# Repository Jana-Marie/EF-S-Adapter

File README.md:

# EF-S-Adapter

Hard- and Firmware to control EF/EF-S lenses. The protocol used has grown since the first generation of EF(-S) lenses hence is a bit extensive with different layers of compatibility. On the physical layer a SPI like interface is used with I2S alike clock-stretching. 

**Please use at your own risk, the hard- and firmware are experimental and can damage your lens!**

### Status

##### v1
 
  - Tested
  - May shorts power rails on lens attachment
  
##### v1.1

 - Tested

### Todo

 - [x] Make lens hotplugable (needs new hardware revision)
 - [ ] Create helper functions (like set_aperture_to(aperture))
 - [ ] Documentation

### Thanks

Thanks to [Jean](https://pickandplace.wordpress.com/2011/10/05/canon-ef-s-protocol-and-electronic-follow-focus/) for this blogpost!

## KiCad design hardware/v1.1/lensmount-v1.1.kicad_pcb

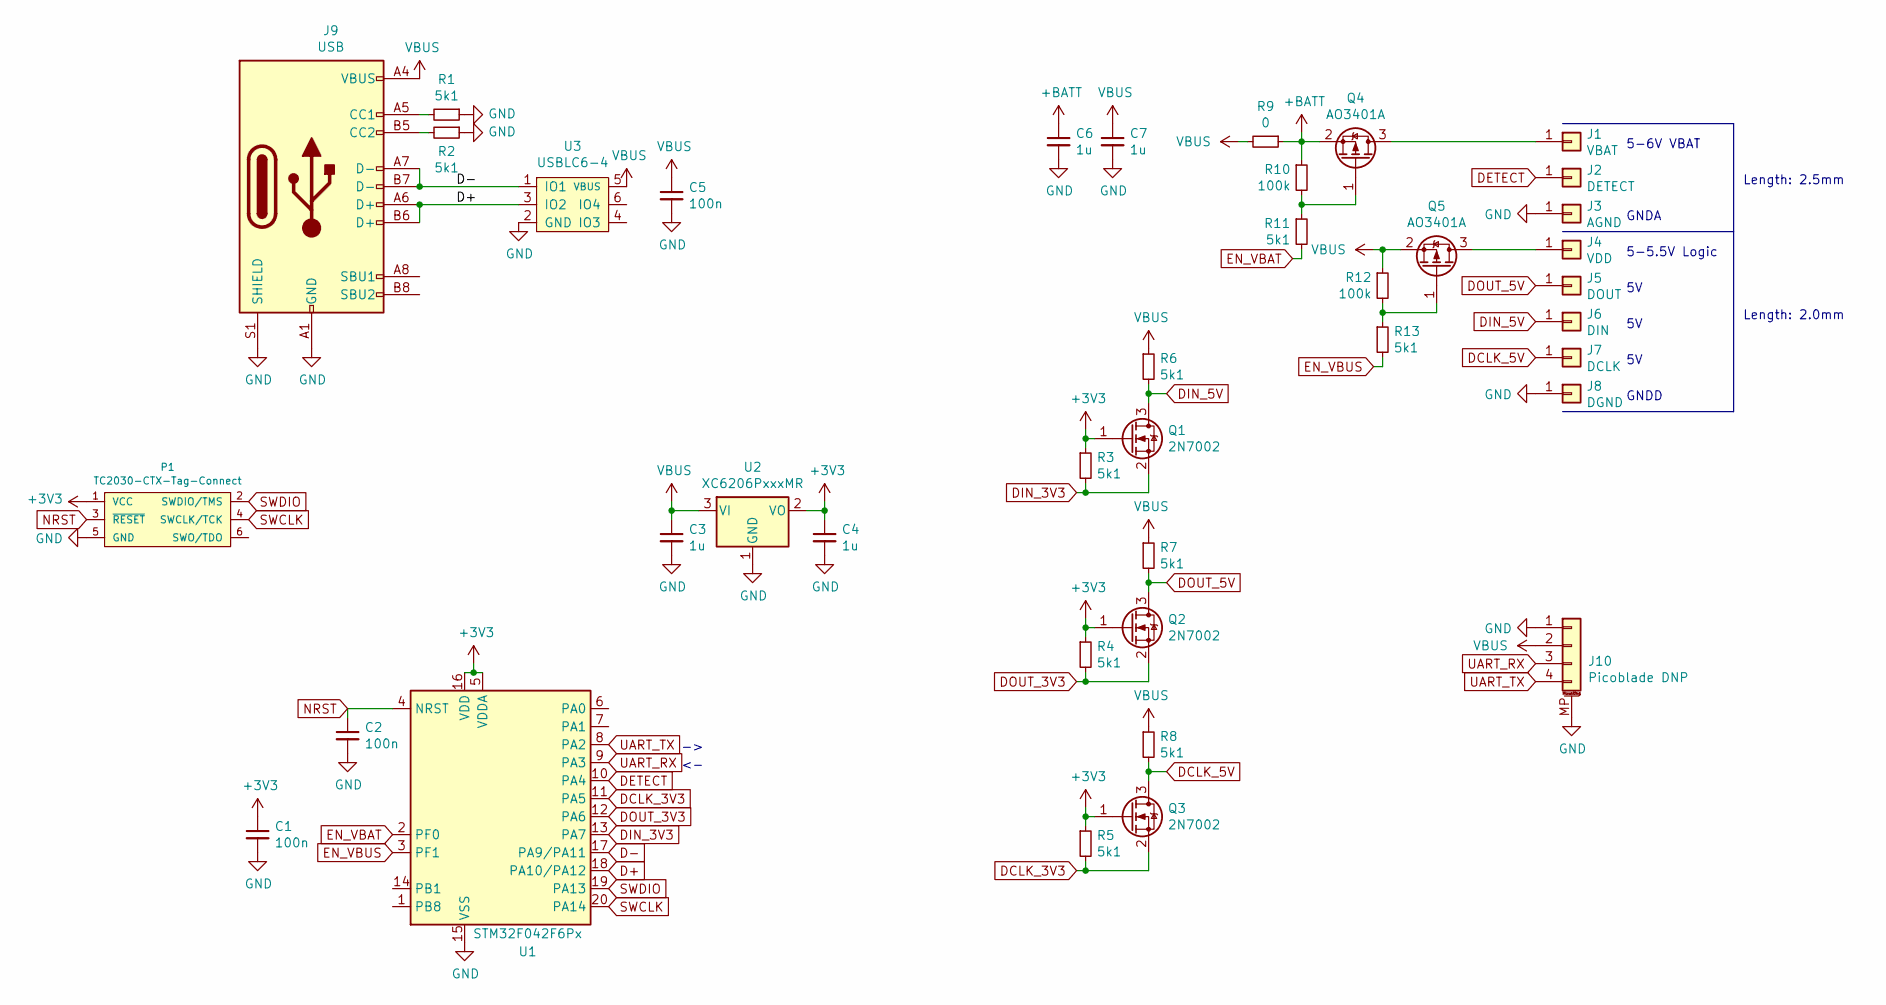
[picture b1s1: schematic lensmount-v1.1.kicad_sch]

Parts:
C1, C2, C5: 100n; C_0402
C3, C4, C6, C7: 1u; C_0603
J1: VBAT; PH-MVF-5365; Mouser 581-709150001025006
J2: DETECT; PH-MVF-5365; Mouser 581-709150001025006
J3: AGND; PH-MVF-5365; Mouser 581-709150001025006
J4: VDD; PH-MVF-5365; Mouser 581-709150001020006
J5: DOUT; PH-MVF-5365; Mouser 581-709150001020006
J6: DIN; PH-MVF-5365; Mouser 581-709150001020006
J7: DCLK; PH-MVF-5365; Mouser 581-709150001020006
J8: DGND; PH-MVF-5365; Mouser 581-709150001020006
J9: USB; USB-C 16Pin
J10: Picoblade DNP; Molex_PicoBlade_53398-0471_1x04-1MP_P1.25mm_Vertical
P1: TC2030-CTX-Tag-Connect; TC2030
Q1, Q2, Q3: 2N7002; SOT-23
Q4, Q5: AO3401A; SOT-23
R1, R2, R3, R4, R5, R6, R7, R8, R11, R13: 5k1; R_0402
R9: 0; R_0402
R10, R12: 100k; R_0402
U1: STM32F042F6Px; TSSOP-20_4.4x6.5mm_P0.65mm
U2: XC6206PxxxMR; SOT-23
U3: USBLC6-4; SOT-23-6

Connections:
+3V3: C1.1, C4.1, P1.1 (VCC), Q1.1 (G), Q2.1 (G), Q3.1 (G), R3.1, R4.1, R5.1, U1.5 (VDDA), U1.16 (VDD), U2.2 (VO)
+BATT: C6.1, Q4.2 (S), R9.1, R10.1
D+: J9.A6 (D+), J9.B6 (D+), U1.18 (PA10/PA12), U3.3 (IO2)
D-: J9.A7 (D-), J9.B7 (D-), U1.17 (PA9/PA11), U3.1 (IO1)
DCLK_3V3: Q3.2 (S), R5.2, U1.11 (PA5)
DCLK_5V: J7.1, Q3.3 (D), R8.2
DETECT: J2.1, U1.10 (PA4)
DIN_3V3: Q1.2 (S), R3.2, U1.13 (PA7)
DIN_5V: J6.1, Q1.3 (D), R6.2
DOUT_3V3: Q2.2 (S), R4.2, U1.12 (PA6)
DOUT_5V: J5.1, Q2.3 (D), R7.2
EN_VBAT: R11.2, U1.2 (PF0)
EN_VBUS: R13.2, U1.3 (PF1)
GND: C1.2, C2.2, C3.2, C4.2, C5.2, C6.2, C7.2, J3.1, J8.1, J9.A1 (GND), J9.A12 (GND), J9.B1 (GND), J9.B12 (GND), J9.S1 (SHIELD), J10.1, J10.MP (MountPin), P1.5 (GND), R1.1, R2.1, U1.15 (VSS), U2.1 (GND), U3.2 (GND)
NRST: C2.1, P1.3 (~RESET), U1.4 (NRST)
unnamed: J1.1, Q4.3 (D)
unnamed: J4.1, Q5.3 (D)
unnamed: J9.A5 (CC1), R1.2
unnamed: J9.B5 (CC2), R2.2
unnamed: Q4.1 (G), R10.2, R11.1
unnamed: Q5.1 (G), R12.2, R13.1
SWCLK: P1.4 (SWCLK/TCK), U1.20 (PA14)
SWDIO: P1.2 (SWDIO/TMS), U1.19 (PA13)
UART_RX: J10.3, U1.9 (PA3)
UART_TX: J10.4, U1.8 (PA2)
VBUS: C3.1, C5.1, C7.1, J9.A4 (VBUS), J9.A9 (VBUS), J9.B4 (VBUS), J9.B9 (VBUS), J10.2, Q5.2 (S), R6.1, R7.1, R8.1, R9.2, R12.1, U2.3 (VI), U3.5 (VBUS)

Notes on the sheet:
5-6V VBAT
Length: 2.5mm
GNDD
Length: 2.0mm
5-5.5V Logic
GNDA

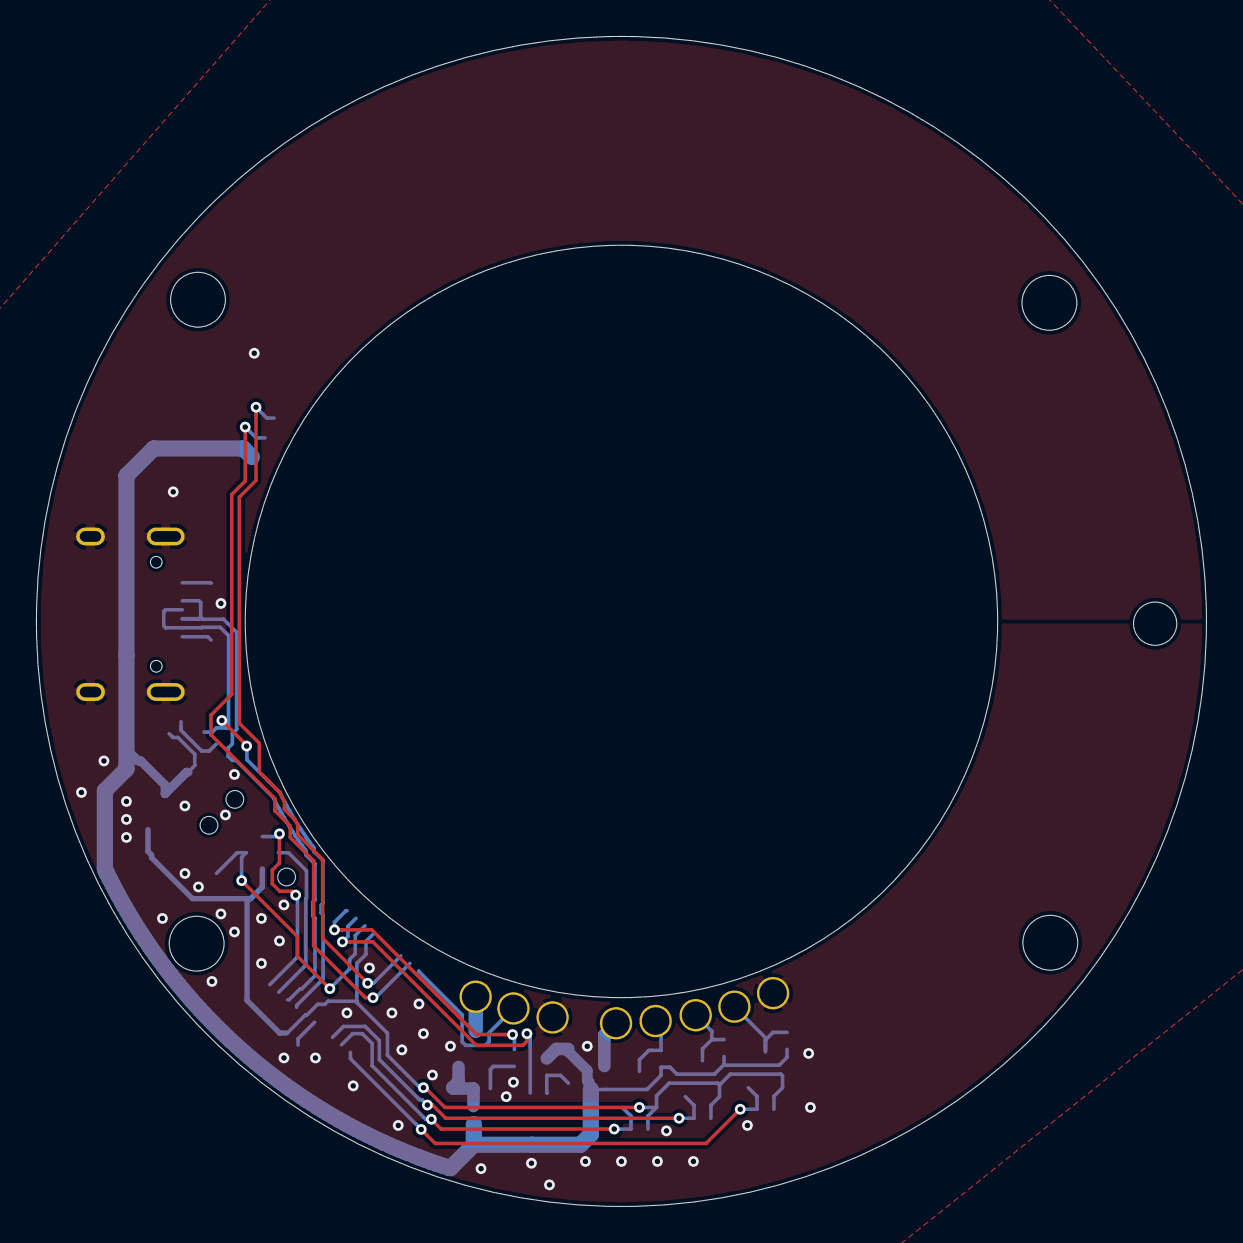
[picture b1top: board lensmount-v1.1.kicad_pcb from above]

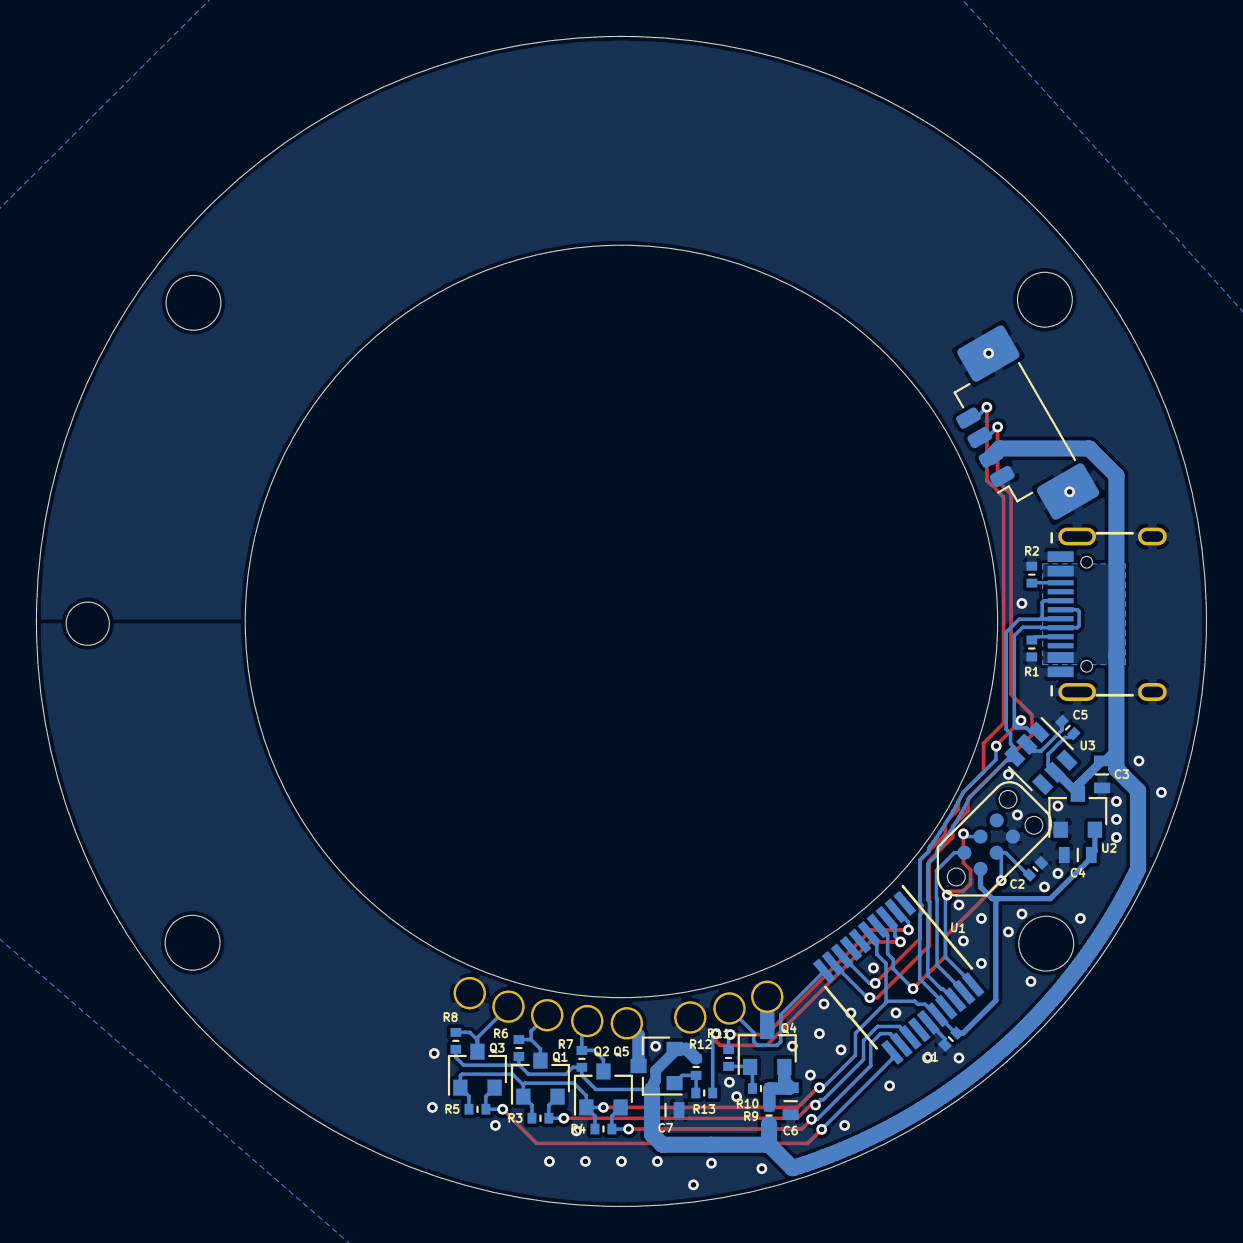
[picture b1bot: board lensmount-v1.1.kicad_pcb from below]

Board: 2 copper layers, 65.0 x 65.0 mm, 39 parts (31 on the bottom side), 26 nets.

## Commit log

2020-10-17 added gitignore
2020-10-17 added hardware
2020-10-17 added CAD
2020-10-17 updated gitignore
2020-10-17 added firmware
2020-10-17 added images
2020-10-17 added hardware v1.1
2020-10-18 updated v1.1
2020-10-24 Create LICENSE
2020-10-24 added pdfs
2022-01-18 updated to kicad6
2024-08-02 add usb firmware & begin python debug console
